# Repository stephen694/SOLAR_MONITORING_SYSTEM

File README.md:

# SOLAR_MONITORING_SYSTEM
SOLAR MONITORING SYSTEM

## Collaborators
1. Masika - Supervisor

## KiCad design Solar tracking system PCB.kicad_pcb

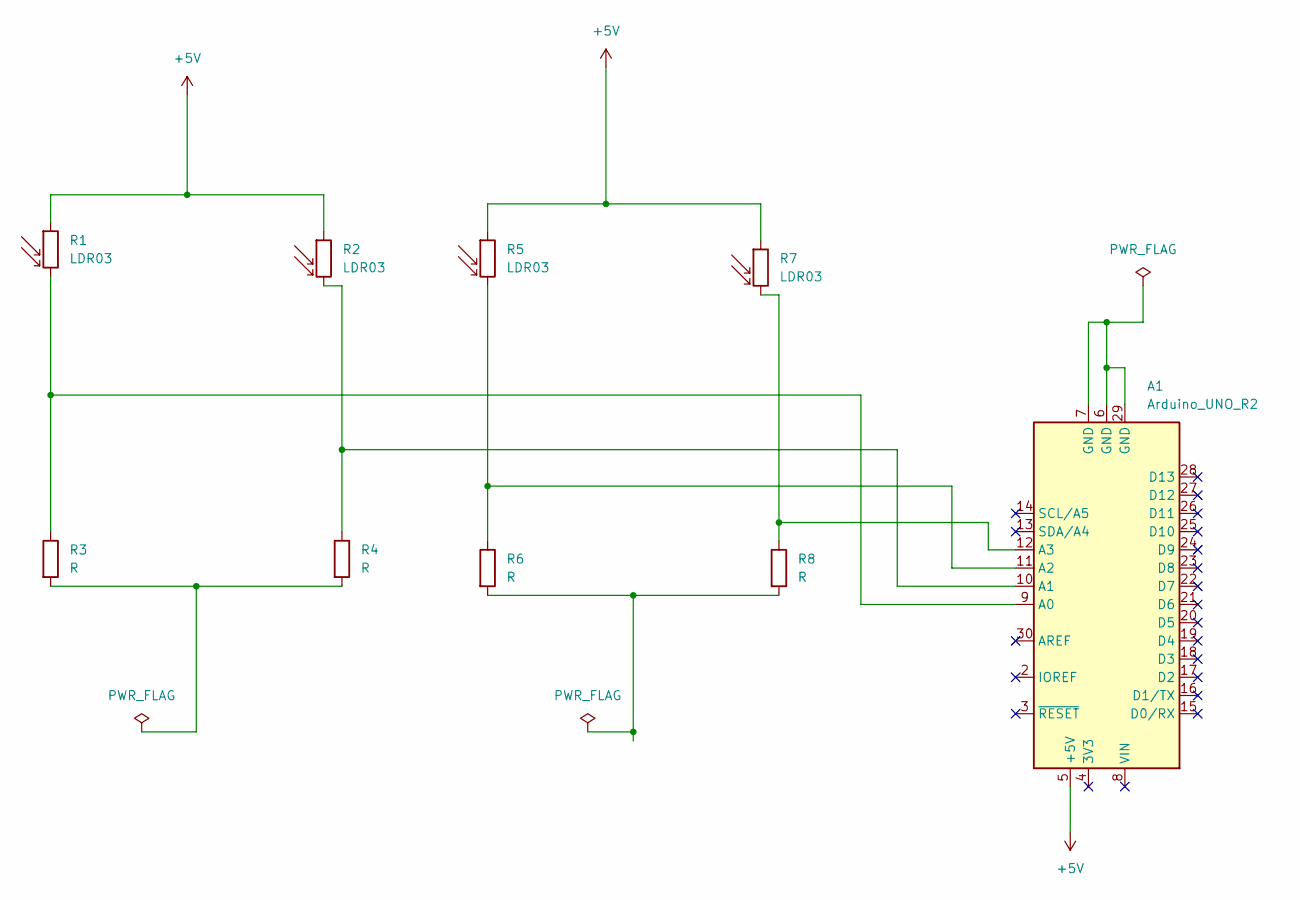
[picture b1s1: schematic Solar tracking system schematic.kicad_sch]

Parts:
A1: Arduino_UNO_R2
R1, R2, R5, R7: LDR03; R_LDR_10x8.5mm_P7.6mm_Vertical
R3, R4, R6, R8: R; R_Axial_DIN0204_L3.6mm_D1.6mm_P5.08mm_Vertical

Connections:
+5V: A1.5 (+5V), R1.1, R2.1, R5.1, R7.1
unnamed: A1.9 (A0), R1.2, R3.1
unnamed: A1.10 (A1), R2.2, R4.1
unnamed: A1.11 (A2), R5.2, R6.1
unnamed: A1.12 (A3), R7.2, R8.1
unnamed: A1.6 (GND), A1.7 (GND), A1.29 (GND)
unnamed: R3.2, R4.2
unnamed: R6.2, R8.2

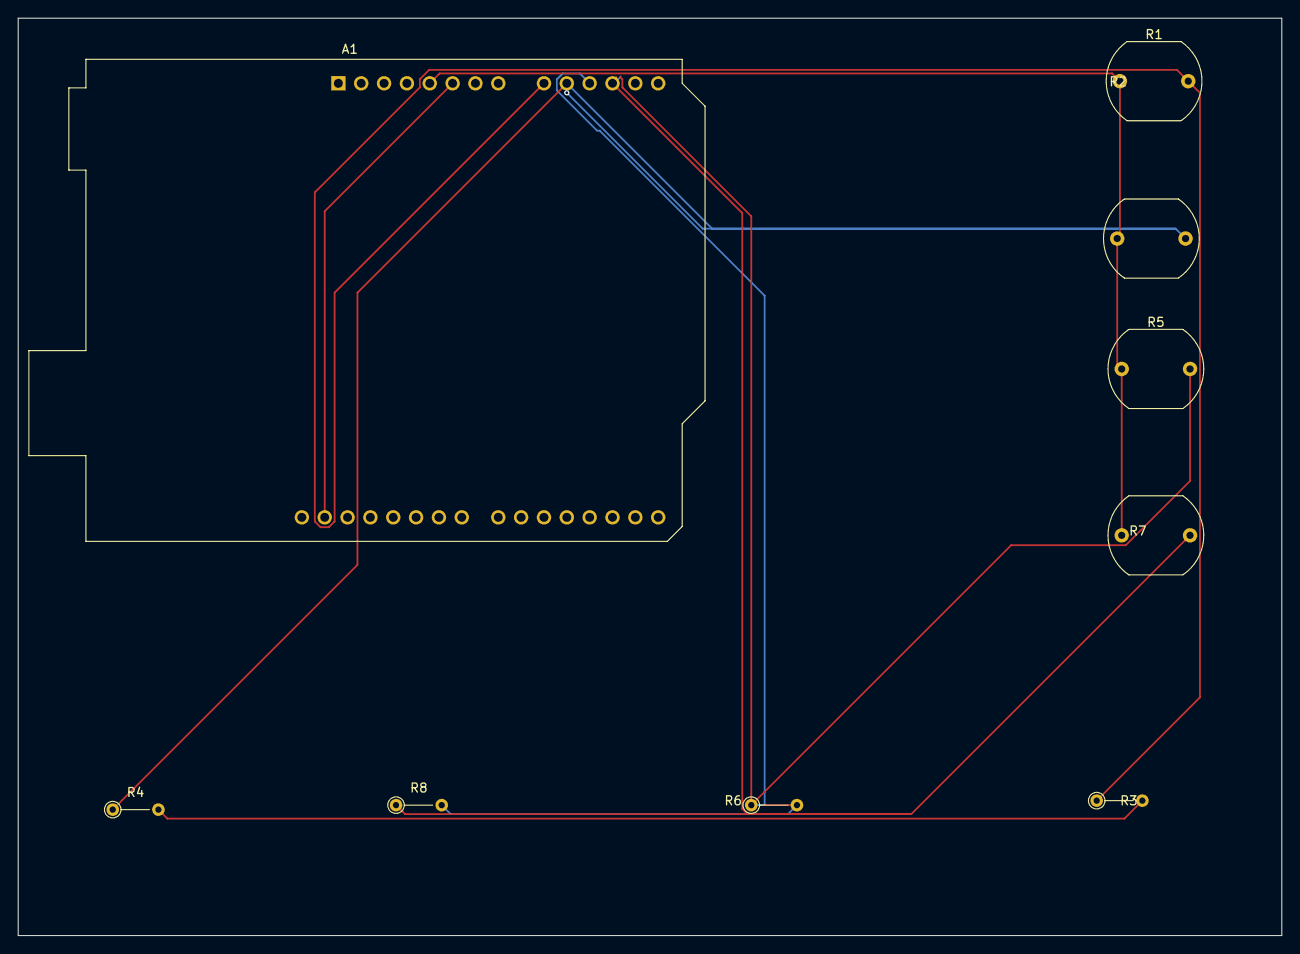
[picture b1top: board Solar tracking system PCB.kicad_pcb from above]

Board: 2 copper layers, 140.5 x 102.0 mm, 9 parts (0 on the bottom side), 8 nets.
